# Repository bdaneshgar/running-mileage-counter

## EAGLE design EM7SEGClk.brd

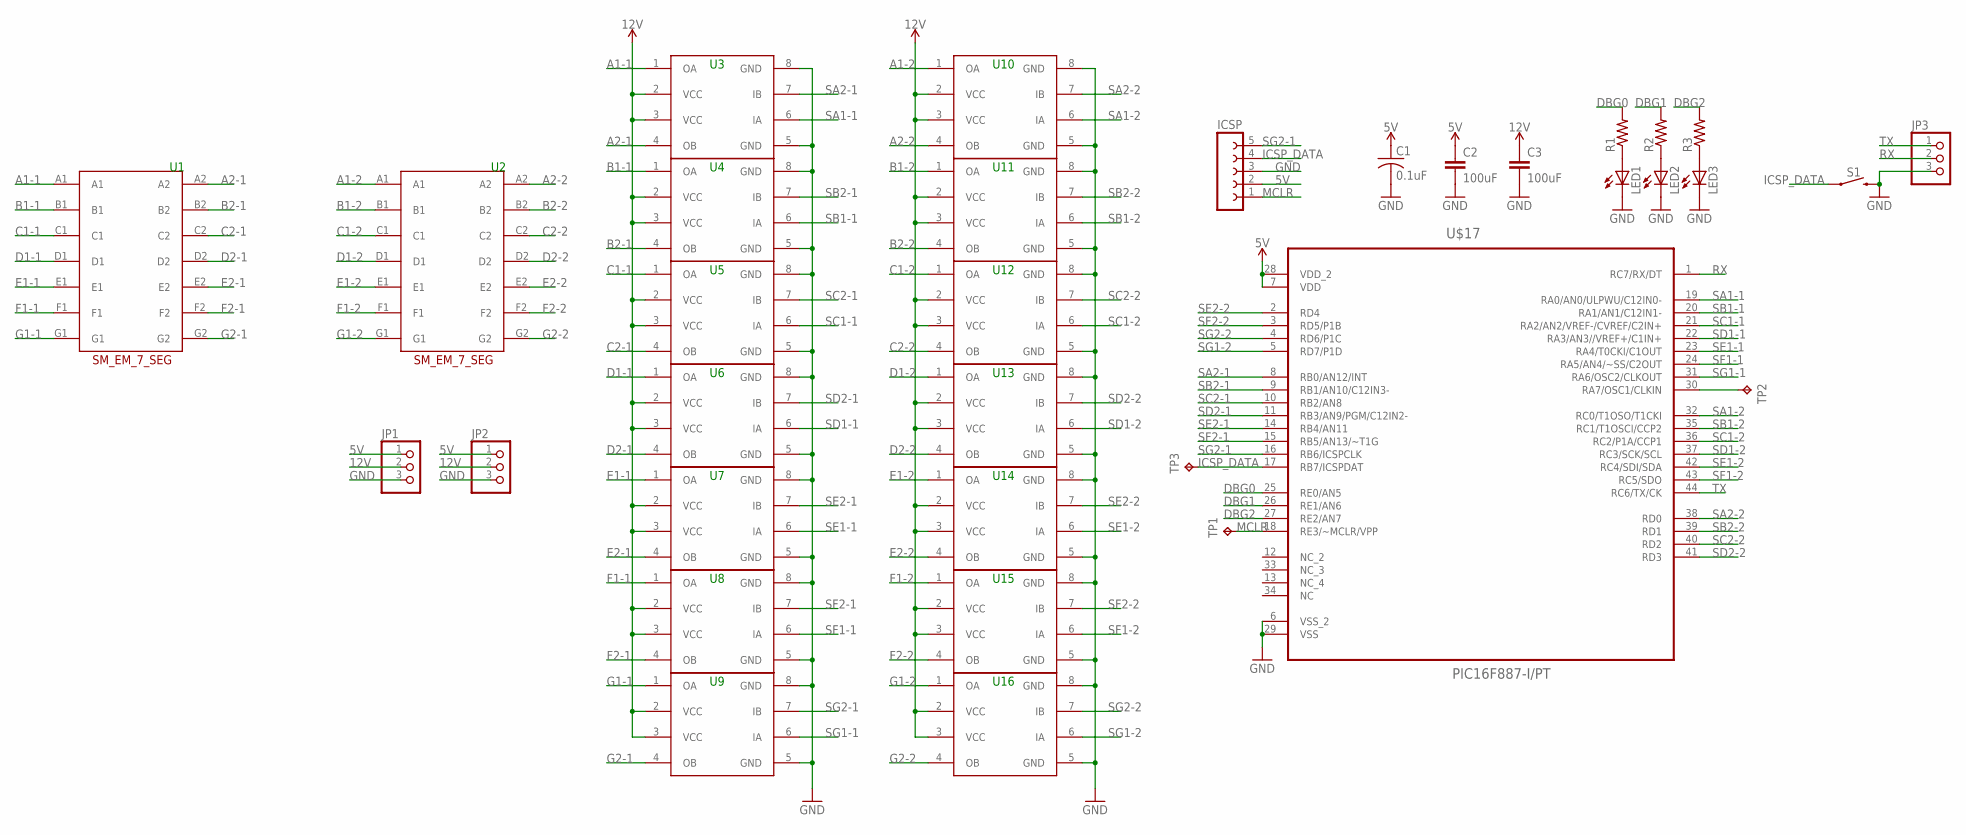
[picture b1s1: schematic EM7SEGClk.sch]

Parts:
C1: 0.1uF; C0805
C2, C3: 100uF; C5B2.5
ICSP: FE05-1
JP1, JP2, JP3: PINHD-1X3CB; 1X03-CLEANBIG
LED1, LED2, LED3: LEDCHIPLED_0805; CHIPLED_0805
R1, R2, R3: R-US_M0805; M0805
S1: MOMENTARY-SWITCH-SPST-PTH-6.0MM; TACTILE_SWITCH_PTH_6.0MM
TP1, TP2, TP3: TPTP16R; TP16R
U$1, U$2: ELECTROMECHANICAL_7_SEG; EM_7_SEG
U$3, U$4, U$5, U$6, U$7, U$8, U$9, U$10, U$14, U$15, U$16, U$140, U$150, U$160: L9110SOP8; SO8
U$17: PIC16F887-I/PT; QFP80P1200X1200X120-44N

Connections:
5V: C1.1, C2.1, ICSP.2, JP1.1, JP2.1, U$17.7 (VDD), U$17.28 (VDD_2)
12V: C3.1, JP1.2, JP2.2, U$3.2 (VCC), U$3.3 (VCC), U$4.2 (VCC), U$4.3 (VCC), U$5.2 (VCC), U$5.3 (VCC), U$6.2 (VCC), U$6.3 (VCC), U$7.2 (VCC), U$7.3 (VCC), U$8.2 (VCC), U$8.3 (VCC), U$9.2 (VCC), U$9.3 (VCC), U$10.2 (VCC), U$10.3 (VCC), U$14.2 (VCC), U$14.3 (VCC), U$15.2 (VCC), U$15.3 (VCC), U$16.2 (VCC), U$16.3 (VCC), U$140.2 (VCC), U$140.3 (VCC), U$150.2 (VCC), U$150.3 (VCC), U$160.2 (VCC), U$160.3 (VCC)
A1-1: U$1.A1, U$3.1 (OA)
A1-2: U$2.A1, U$10.1 (OA)
A2-1: U$1.A2, U$3.4 (OB)
A2-2: U$2.A2, U$10.4 (OB)
B1-1: U$1.B1, U$4.1 (OA)
B1-2: U$2.B1, U$140.1 (OA)
B2-1: U$1.B2, U$4.4 (OB)
B2-2: U$2.B2, U$140.4 (OB)
C1-1: U$1.C1, U$5.1 (OA)
C1-2: U$2.C1, U$150.1 (OA)
C2-1: U$1.C2, U$5.4 (OB)
C2-2: U$2.C2, U$150.4 (OB)
D1-1: U$1.D1, U$6.1 (OA)
D1-2: U$2.D1, U$160.1 (OA)
D2-1: U$1.D2, U$6.4 (OB)
D2-2: U$2.D2, U$160.4 (OB)
DBG0: R1.2, U$17.25 (RE0/AN5)
DBG1: R2.2, U$17.26 (RE1/AN6)
DBG2: R3.2, U$17.27 (RE2/AN7)
E1-1: U$1.E1, U$7.1 (OA)
E1-2: U$2.E1, U$14.1 (OA)
E2-1: U$1.E2, U$7.4 (OB)
E2-2: U$2.E2, U$14.4 (OB)
F1-1: U$1.F1, U$8.1 (OA)
F1-2: U$2.F1, U$15.1 (OA)
F2-1: U$1.F2, U$8.4 (OB)
F2-2: U$2.F2, U$15.4 (OB)
G1-1: U$1.G1, U$9.1 (OA)
G1-2: U$2.G1, U$16.1 (OA)
G2-1: U$1.G2, U$9.4 (OB)
G2-2: U$2.G2, U$16.4 (OB)
GND: C1.2, C2.2, C3.2, ICSP.3, JP1.3, JP2.3, JP3.3, LED1.C, LED2.C, LED3.C, S1.3 (2), U$3.5 (GND), U$3.8 (GND), U$4.5 (GND), U$4.8 (GND), U$5.5 (GND), U$5.8 (GND), U$6.5 (GND), U$6.8 (GND), U$7.5 (GND), U$7.8 (GND), U$8.5 (GND), U$8.8 (GND), U$9.5 (GND), U$9.8 (GND), U$10.5 (GND), U$10.8 (GND), U$14.5 (GND), U$14.8 (GND), U$15.5 (GND), U$15.8 (GND), U$16.5 (GND), U$16.8 (GND), U$17.6 (VSS_2), U$17.29 (VSS), U$140.5 (GND), U$140.8 (GND), U$150.5 (GND), U$150.8 (GND), U$160.5 (GND), U$160.8 (GND)
ICSP_DATA: ICSP.4, S1.1, TP3.TP, U$17.17 (RB7/ICSPDAT)
MCLR: ICSP.1, TP1.TP, U$17.18 (RE3/~MCLR/VPP)
unnamed: LED1.A, R1.1
unnamed: LED2.A, R2.1
unnamed: LED3.A, R3.1
unnamed: TP2.TP, U$17.30 (RA7/OSC1/CLKIN)
RX: JP3.2, U$17.1 (RC7/RX/DT)
SA1-1: U$3.6 (IA), U$17.19 (RA0/AN0/ULPWU/C12IN0-)
SA1-2: U$10.6 (IA), U$17.32 (RC0/T1OSO/T1CKI)
SA2-1: U$3.7 (IB), U$17.8 (RB0/AN12/INT)
SA2-2: U$10.7 (IB), U$17.38 (RD0)
SB1-1: U$4.6 (IA), U$17.20 (RA1/AN1/C12IN1-)
SB1-2: U$17.35 (RC1/T1OSCI/CCP2), U$140.6 (IA)
SB2-1: U$4.7 (IB), U$17.9 (RB1/AN10/C12IN3-)
SB2-2: U$17.39 (RD1), U$140.7 (IB)
SC1-1: U$5.6 (IA), U$17.21 (RA2/AN2/VREF-/CVREF/C2IN+)
SC1-2: U$17.36 (RC2/P1A/CCP1), U$150.6 (IA)
SC2-1: U$5.7 (IB), U$17.10 (RB2/AN8)
SC2-2: U$17.40 (RD2), U$150.7 (IB)
SD1-1: U$6.6 (IA), U$17.22 (RA3/AN3//VREF+/C1IN+)
SD1-2: U$17.37 (RC3/SCK/SCL), U$160.6 (IA)
SD2-1: U$6.7 (IB), U$17.11 (RB3/AN9/PGM/C12IN2-)
SD2-2: U$17.41 (RD3), U$160.7 (IB)
SE1-1: U$7.6 (IA), U$17.23 (RA4/T0CKI/C1OUT)
SE1-2: U$14.6 (IA), U$17.42 (RC4/SDI/SDA)
SE2-1: U$7.7 (IB), U$17.14 (RB4/AN11)
SE2-2: U$14.7 (IB), U$17.2 (RD4)
SF1-1: U$8.6 (IA), U$17.24 (RA5/AN4/~SS/C2OUT)
SF1-2: U$15.6 (IA), U$17.43 (RC5/SDO)
SF2-1: U$8.7 (IB), U$17.15 (RB5/AN13/~T1G)
SF2-2: U$15.7 (IB), U$17.3 (RD5/P1B)
SG1-1: U$9.6 (IA), U$17.31 (RA6/OSC2/CLKOUT)
SG1-2: U$16.6 (IA), U$17.5 (RD7/P1D)
SG2-1: ICSP.5, U$9.7 (IB), U$17.16 (RB6/ICSPCLK)
SG2-2: U$16.7 (IB), U$17.4 (RD6/P1C)
TX: JP3.1, U$17.44 (RC6/TX/CK)

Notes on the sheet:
U10
U11
U12
U13
U14
U15
U16

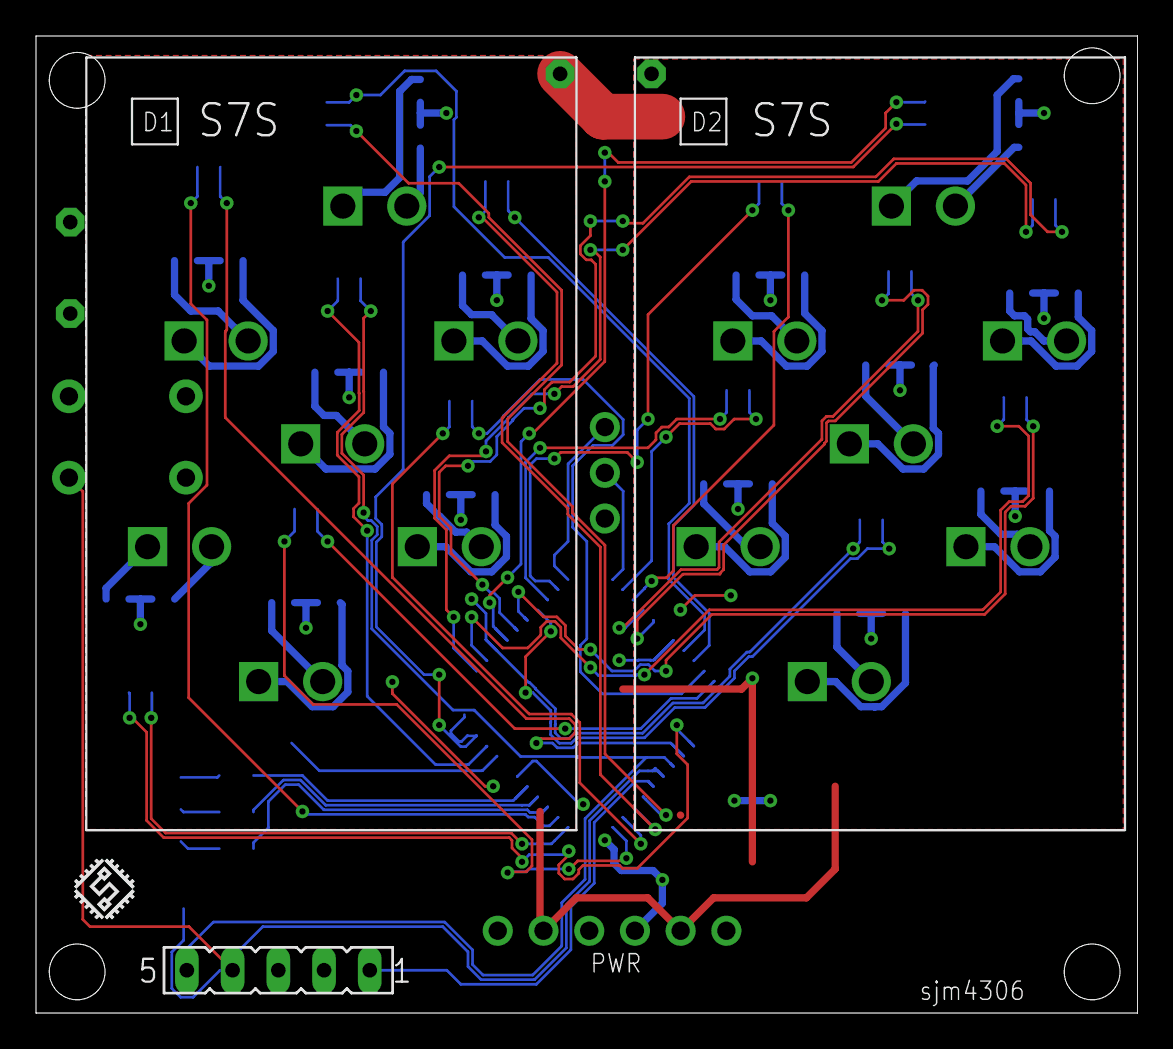
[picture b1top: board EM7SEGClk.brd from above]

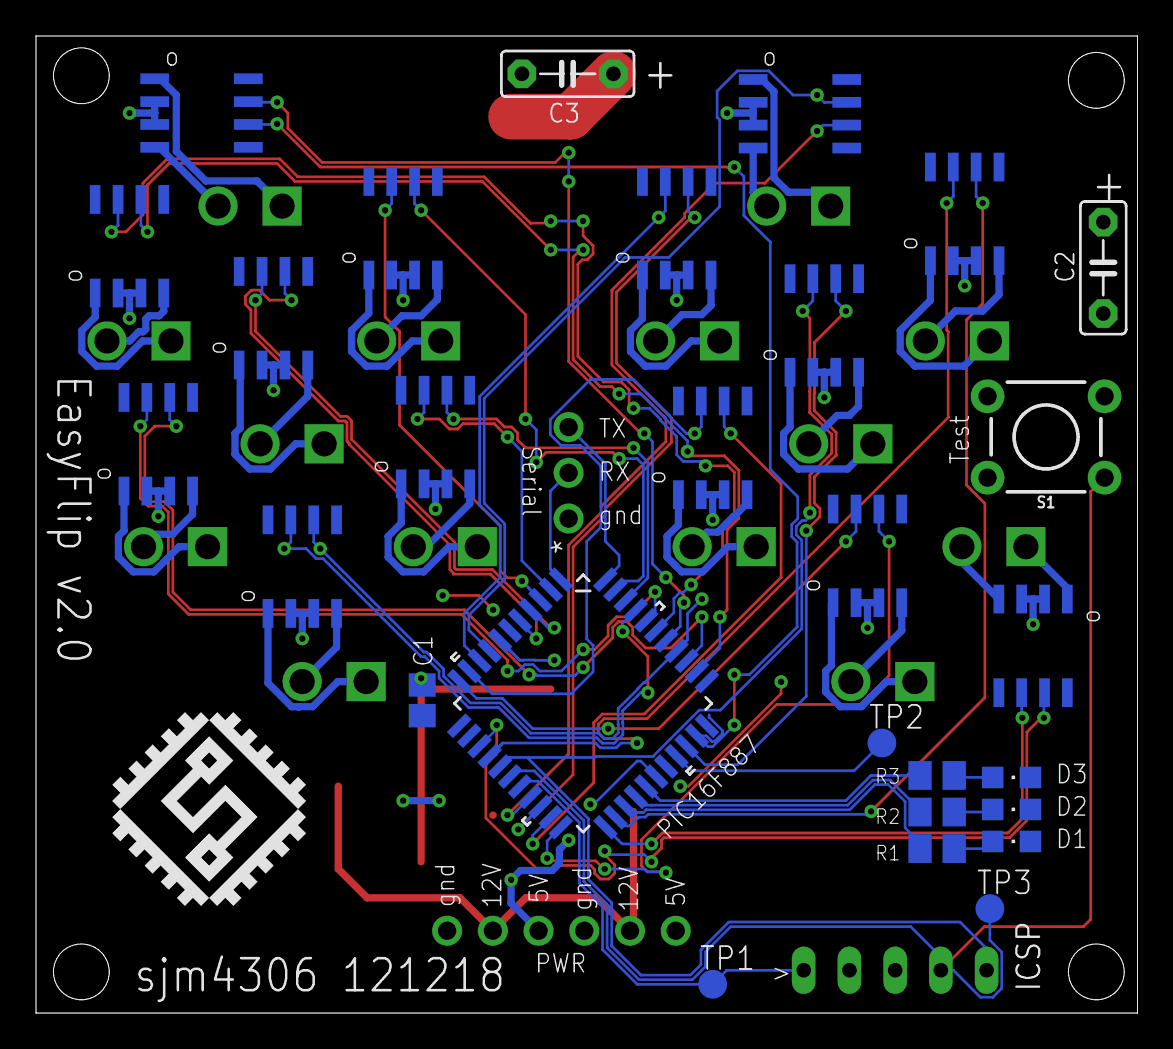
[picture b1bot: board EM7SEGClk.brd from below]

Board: 2 copper layers, 61.2 x 54.3 mm, 36 parts (29 on the bottom side), 70 nets.

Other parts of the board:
U$11: SJM4306_LOGO_MEDIUM
U$13: SJM4306_LOGO_SMALL

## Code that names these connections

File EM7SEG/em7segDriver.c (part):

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#define bit_clr(var,bitno) ((var) &= ~(1 << (bitno)))

//Access I/0 via macros
#define SEGA	RA0		//EM Low Side Mux'd Segments
#define SEGB	RA1
#define SEGC	RA2
#define SEGD	RA3
#define SEGE	RA4
#define SEGF	RA5
#define SEGG	RA6

#define SC1		RC0		//High Side Set/Clr Ctrl
#define SC2		RC1
#define DISP1	RC2		//Select Enable for Digit 1 or 2
#define DISP2	RC3

#define TX		RC6		//UART Serial Slave Port
#define RX		RC7

#define Test	RB0		//Test button
#define Debug	RA7		//Debug LED

//Gloabal Variables////////////////////////////////////////
unsigned char m_address = 0;	//assigned device programmed address, will execute commands directed at this address, EEPROM address 0x00 holds this address
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

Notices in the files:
parts and their libraries:
SparkFun-Switches: Licensing: Creative Commons ShareAlike 4.0 International - https://creativecommons.org/licenses/by-sa/4.0
